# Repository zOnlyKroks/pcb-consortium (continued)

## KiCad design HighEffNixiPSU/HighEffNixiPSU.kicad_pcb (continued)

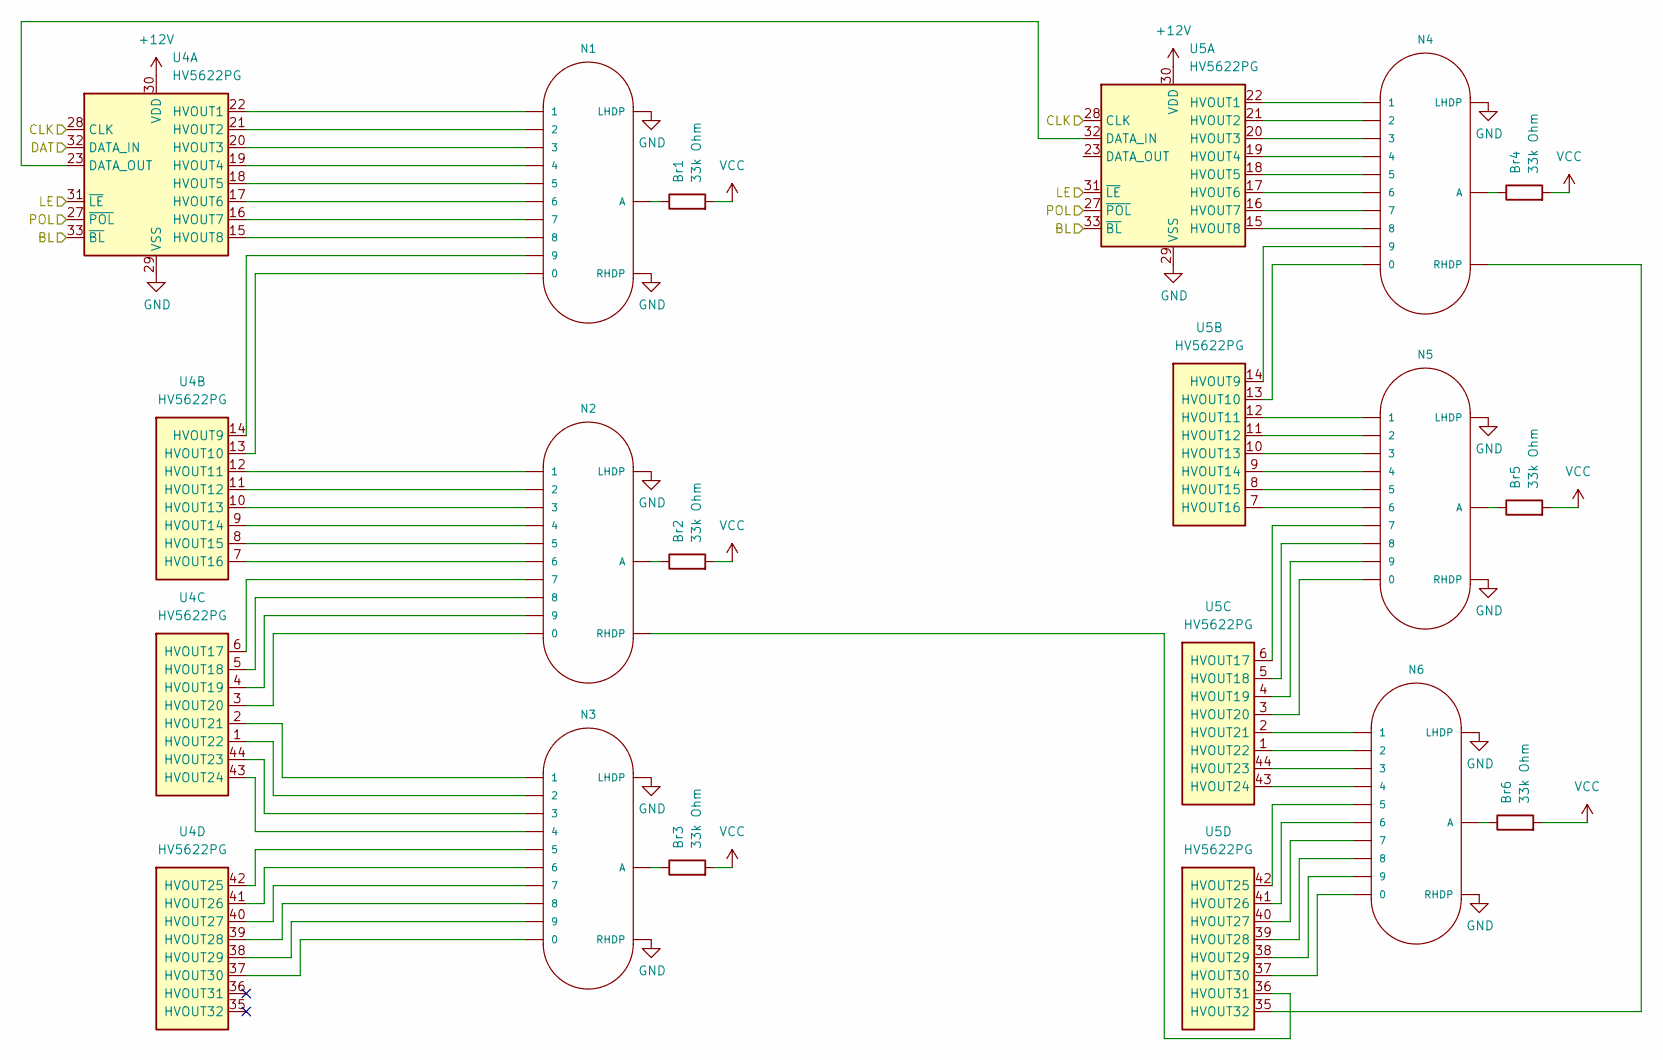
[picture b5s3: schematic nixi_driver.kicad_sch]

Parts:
Br1, Br2, Br3, Br4, Br5, Br6: 33k Ohm; R_1210_3225Metric; LCSC Part # C2775731
N1, N2, N3, N4, N5, N6: IN-16; nixies-us-IN-16
U4, U5: HV5622PG; PQFP-44_10x10mm_P0.8mm; LCSC Part # C220637

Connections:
+12V: U4.30 (VDD), U5.30 (VDD); also elsewhere on the board
/mcu/BL: U4.33 (~BL), U5.33 (~BL); also elsewhere on the board
/mcu/CLK: U4.28 (CLK), U5.28 (CLK); also elsewhere on the board
/mcu/DAT: U4.32 (DATA_IN); also elsewhere on the board
/mcu/LE: U4.31 (~LE), U5.31 (~LE); also elsewhere on the board
/mcu/POL: U4.27 (~POL), U5.27 (~POL); also elsewhere on the board
GND: N1.LHDP, N1.RHDP, N2.LHDP, N3.LHDP, N3.RHDP, N4.LHDP, N5.LHDP, N5.RHDP, N6.LHDP, N6.RHDP, U4.29 (VSS), U5.29 (VSS); also elsewhere on the board
unnamed: Br1.1, N1.A
unnamed: Br2.1, N2.A
unnamed: Br3.1, N3.A
unnamed: Br4.1, N4.A
unnamed: Br5.1, N5.A
unnamed: Br6.1, N6.A
unnamed: U4.23 (DATA_OUT), U5.32 (DATA_IN)
unnamed: N1.1, U4.22 (HVOUT1)
unnamed: N1.2, U4.21 (HVOUT2)
unnamed: N1.3, U4.20 (HVOUT3)
unnamed: N1.4, U4.19 (HVOUT4)
unnamed: N1.5, U4.18 (HVOUT5)
unnamed: N1.6, U4.17 (HVOUT6)
unnamed: N1.7, U4.16 (HVOUT7)
unnamed: N1.8, U4.15 (HVOUT8)
unnamed: N1.9, U4.14 (HVOUT9)
unnamed: N1.0, U4.13 (HVOUT10)
unnamed: N2.1, U4.12 (HVOUT11)
unnamed: N2.2, U4.11 (HVOUT12)
unnamed: N2.3, U4.10 (HVOUT13)
unnamed: N2.4, U4.9 (HVOUT14)
unnamed: N2.5, U4.8 (HVOUT15)
unnamed: N2.6, U4.7 (HVOUT16)
unnamed: N2.7, U4.6 (HVOUT17)
unnamed: N2.8, U4.5 (HVOUT18)
unnamed: N2.9, U4.4 (HVOUT19)
unnamed: N2.0, U4.3 (HVOUT20)
unnamed: N3.1, U4.2 (HVOUT21)
unnamed: N3.2, U4.1 (HVOUT22)
unnamed: N3.3, U4.44 (HVOUT23)
unnamed: N3.4, U4.43 (HVOUT24)
unnamed: N3.5, U4.42 (HVOUT25)
unnamed: N3.6, U4.41 (HVOUT26)
unnamed: N3.7, U4.40 (HVOUT27)
unnamed: N3.8, U4.39 (HVOUT28)
unnamed: N3.9, U4.38 (HVOUT29)
unnamed: N3.0, U4.37 (HVOUT30)
unnamed: N4.1, U5.22 (HVOUT1)
unnamed: N4.2, U5.21 (HVOUT2)
unnamed: N4.3, U5.20 (HVOUT3)
unnamed: N4.4, U5.19 (HVOUT4)
unnamed: N4.5, U5.18 (HVOUT5)
unnamed: N4.6, U5.17 (HVOUT6)
unnamed: N4.7, U5.16 (HVOUT7)
unnamed: N4.8, U5.15 (HVOUT8)
unnamed: N4.9, U5.14 (HVOUT9)
unnamed: N4.0, U5.13 (HVOUT10)
unnamed: N5.1, U5.12 (HVOUT11)
unnamed: N5.2, U5.11 (HVOUT12)
unnamed: N5.3, U5.10 (HVOUT13)
unnamed: N5.4, U5.9 (HVOUT14)
unnamed: N5.5, U5.8 (HVOUT15)
unnamed: N5.6, U5.7 (HVOUT16)
unnamed: N5.7, U5.6 (HVOUT17)
unnamed: N5.8, U5.5 (HVOUT18)
unnamed: N5.9, U5.4 (HVOUT19)
unnamed: N5.0, U5.3 (HVOUT20)
unnamed: N6.1, U5.2 (HVOUT21)
unnamed: N6.2, U5.1 (HVOUT22)
unnamed: N6.3, U5.44 (HVOUT23)
unnamed: N6.4, U5.43 (HVOUT24)
unnamed: N6.5, U5.42 (HVOUT25)
unnamed: N6.6, U5.41 (HVOUT26)
unnamed: N6.7, U5.40 (HVOUT27)
unnamed: N6.8, U5.39 (HVOUT28)
unnamed: N6.9, U5.38 (HVOUT29)
unnamed: N6.0, U5.37 (HVOUT30)
unnamed: N2.RHDP, U5.36 (HVOUT31)
unnamed: N4.RHDP, U5.35 (HVOUT32)
VCC: Br1.2, Br2.2, Br3.2, Br4.2, Br5.2, Br6.2; also elsewhere on the board

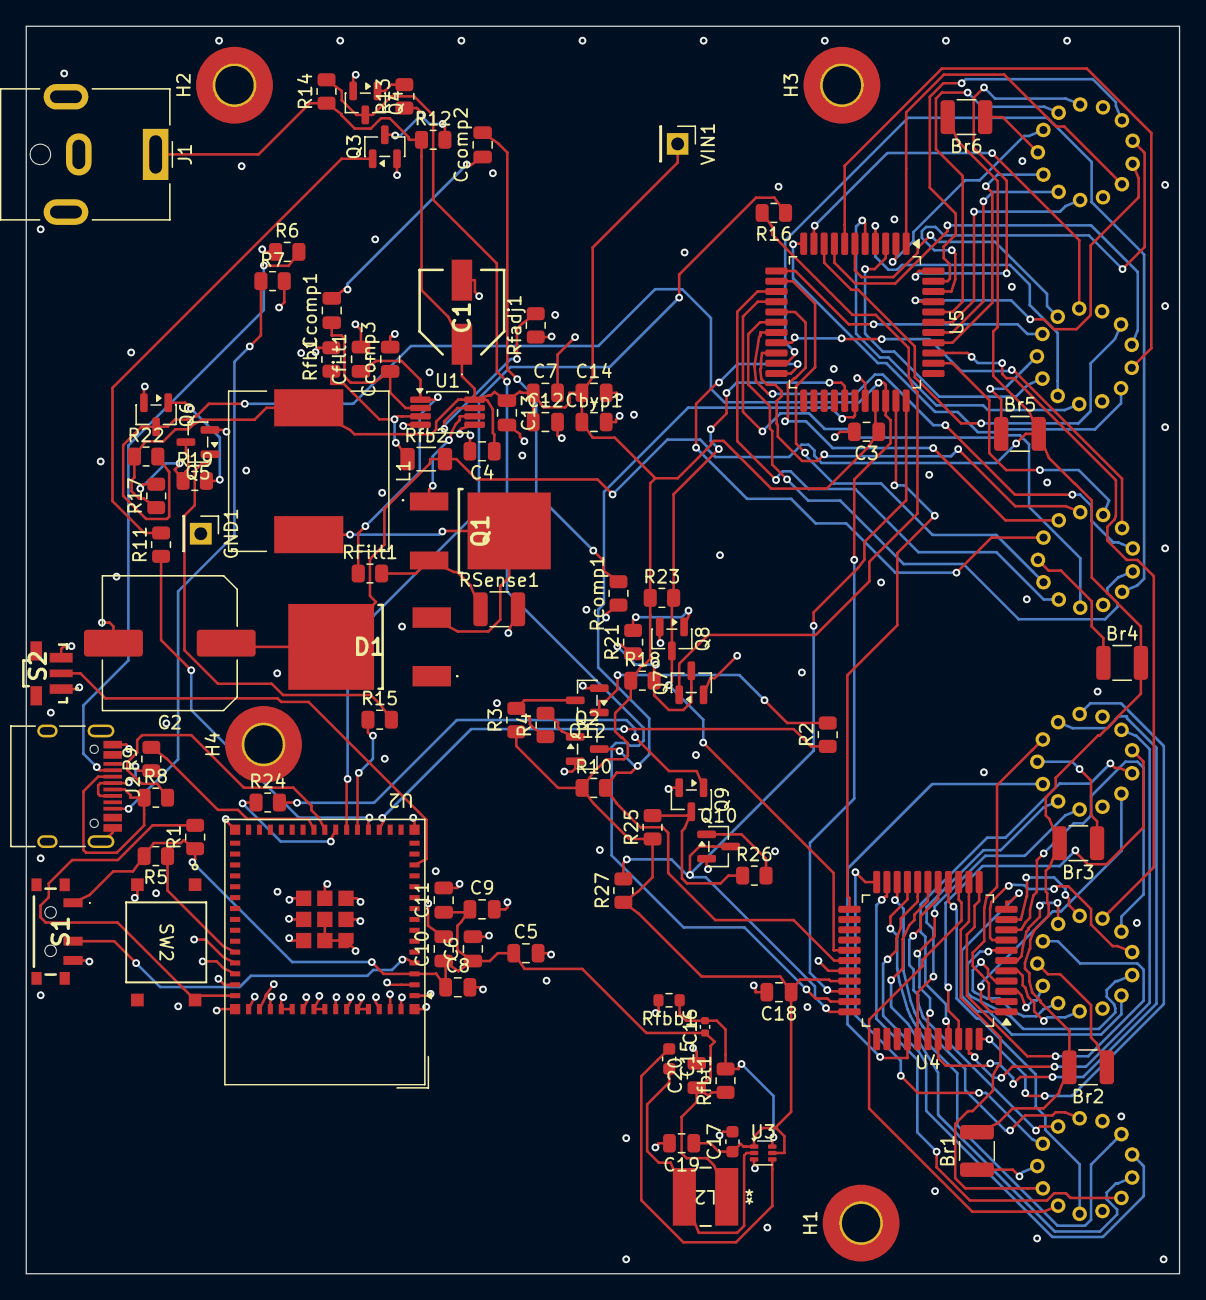
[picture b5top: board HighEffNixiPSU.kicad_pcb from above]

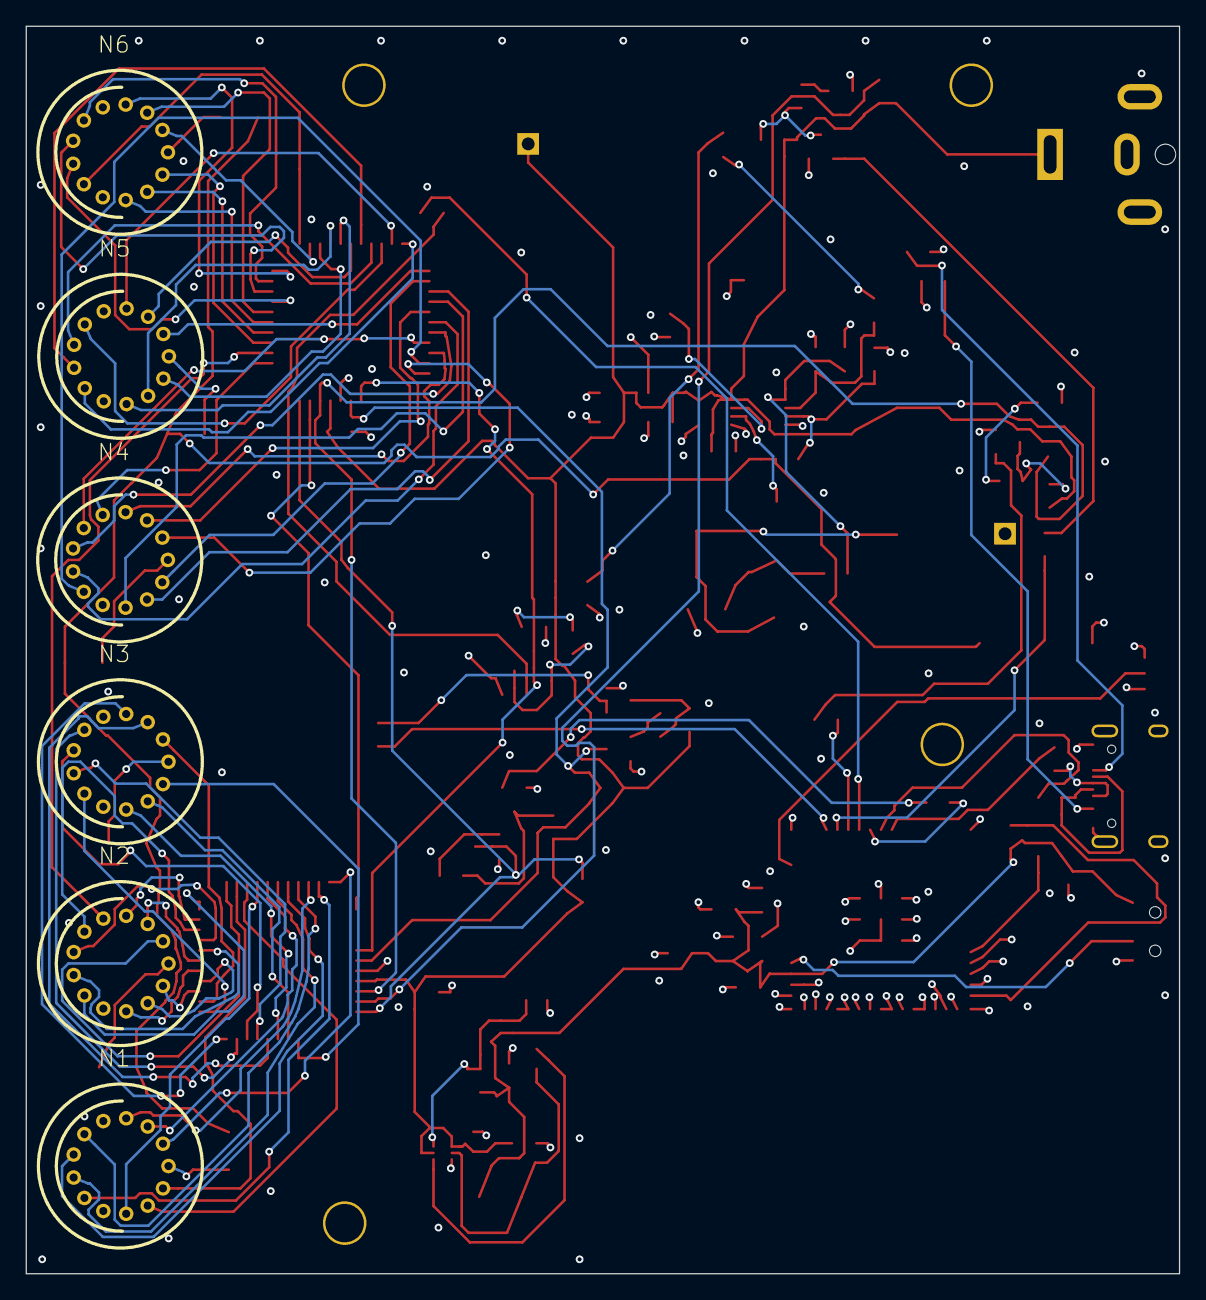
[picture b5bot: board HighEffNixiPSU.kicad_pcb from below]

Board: 4 copper layers, 90.0 x 97.4 mm, 101 parts (6 on the bottom side), 120 nets.

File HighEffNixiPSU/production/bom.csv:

Designator,Footprint,Quantity,Value,LCSC Part #
"BR1, BR2, BR3, BR4, BR5, BR6",1210,6,33k Ohm,C2775731
C1,EEE1AA101SP,1,EEE-FT1V680AP,C413520
"C10, C11, C6, C8, C9",0805,5,100nF,C28233
C5,0805,1,10uF,C15850
CBYP1,0805,1,100nF,C784084
"CCOMP1, CCOMP2",0805,2,1.5nF,C1717
CCOMP3,0805,1,150pF,C2168780
CFILT1,0805,1,10 pF,C107107
D1,STTH506BTR,1,STTH506B,C283501
"GND1, VIN1",PinHeader_1x01_P2.54mm_Vertical,2,Conn_01x01,C492400
IC1,SOT230P700X180-4N,1,AZ1117CH-3.3TRG1,C92102
J1,BarrelJack_CUI_PJ-063AH_Horizontal,1,Jack-DC,C22434582
J2,USB_C_Receptacle_HRO_TYPE-C-31-M-12,1,USB_C_Receptacle_USB2.0,C165948
L1,CYH127-330UH,1,CYH127-330UH,C2929508
"N1, N2, N3, N4, N5, N6",nixies-us-IN-16,6,IN-16,
Q1,FQD16N25CTM,1,FQD16N25CTM,C415866
"Q10, Q12, Q2, Q3, Q4, Q5, Q6, Q7, Q8, Q9",SOT-23,10,MMBTA06,C20069139
"R1, R11, R12, R13, R15, R16, R17, R18, R19, R2, R21, R24, R25, R26, R3, R4, R5",0805,17,10k,C17414
"R10, R14, R22, R23, R27",0805,5,4.7k,C17673
"R6, R7",0805,2,5.1k,C27834
"R8, R9",0805,2,22,C17561
RCOMP1,0805,1,162 kOhm,C47115899
RFADJ1,0805,1,147 kOhm,C47115874
RFB1,0805,1,8.06 kOhm,C857074
RFB2,1206,1,1.2MOhm,C36337
RFILT1,0805,1,100 Ohm,C17408
RSENSE1,1210,1,33 mOhm,C723419
S1,SSSS811101,1,SSSS811101,C109335
S2,TL3340,1,TL3340AF160QG,C2886925
SW2,KH-6X6X5H-STM_SKE,1,EN,C2837531 
U1,VSSOP-8_3x3mm_P0.65mm,1,LM3478MM,C9404
U2,ESP32-S2-MINI-1,1,ESP32-S3-MINI-1,C2913206 
"U4, U5",PQFP-44_10x10mm_P0.8mm,2,HV5622PG,C220637

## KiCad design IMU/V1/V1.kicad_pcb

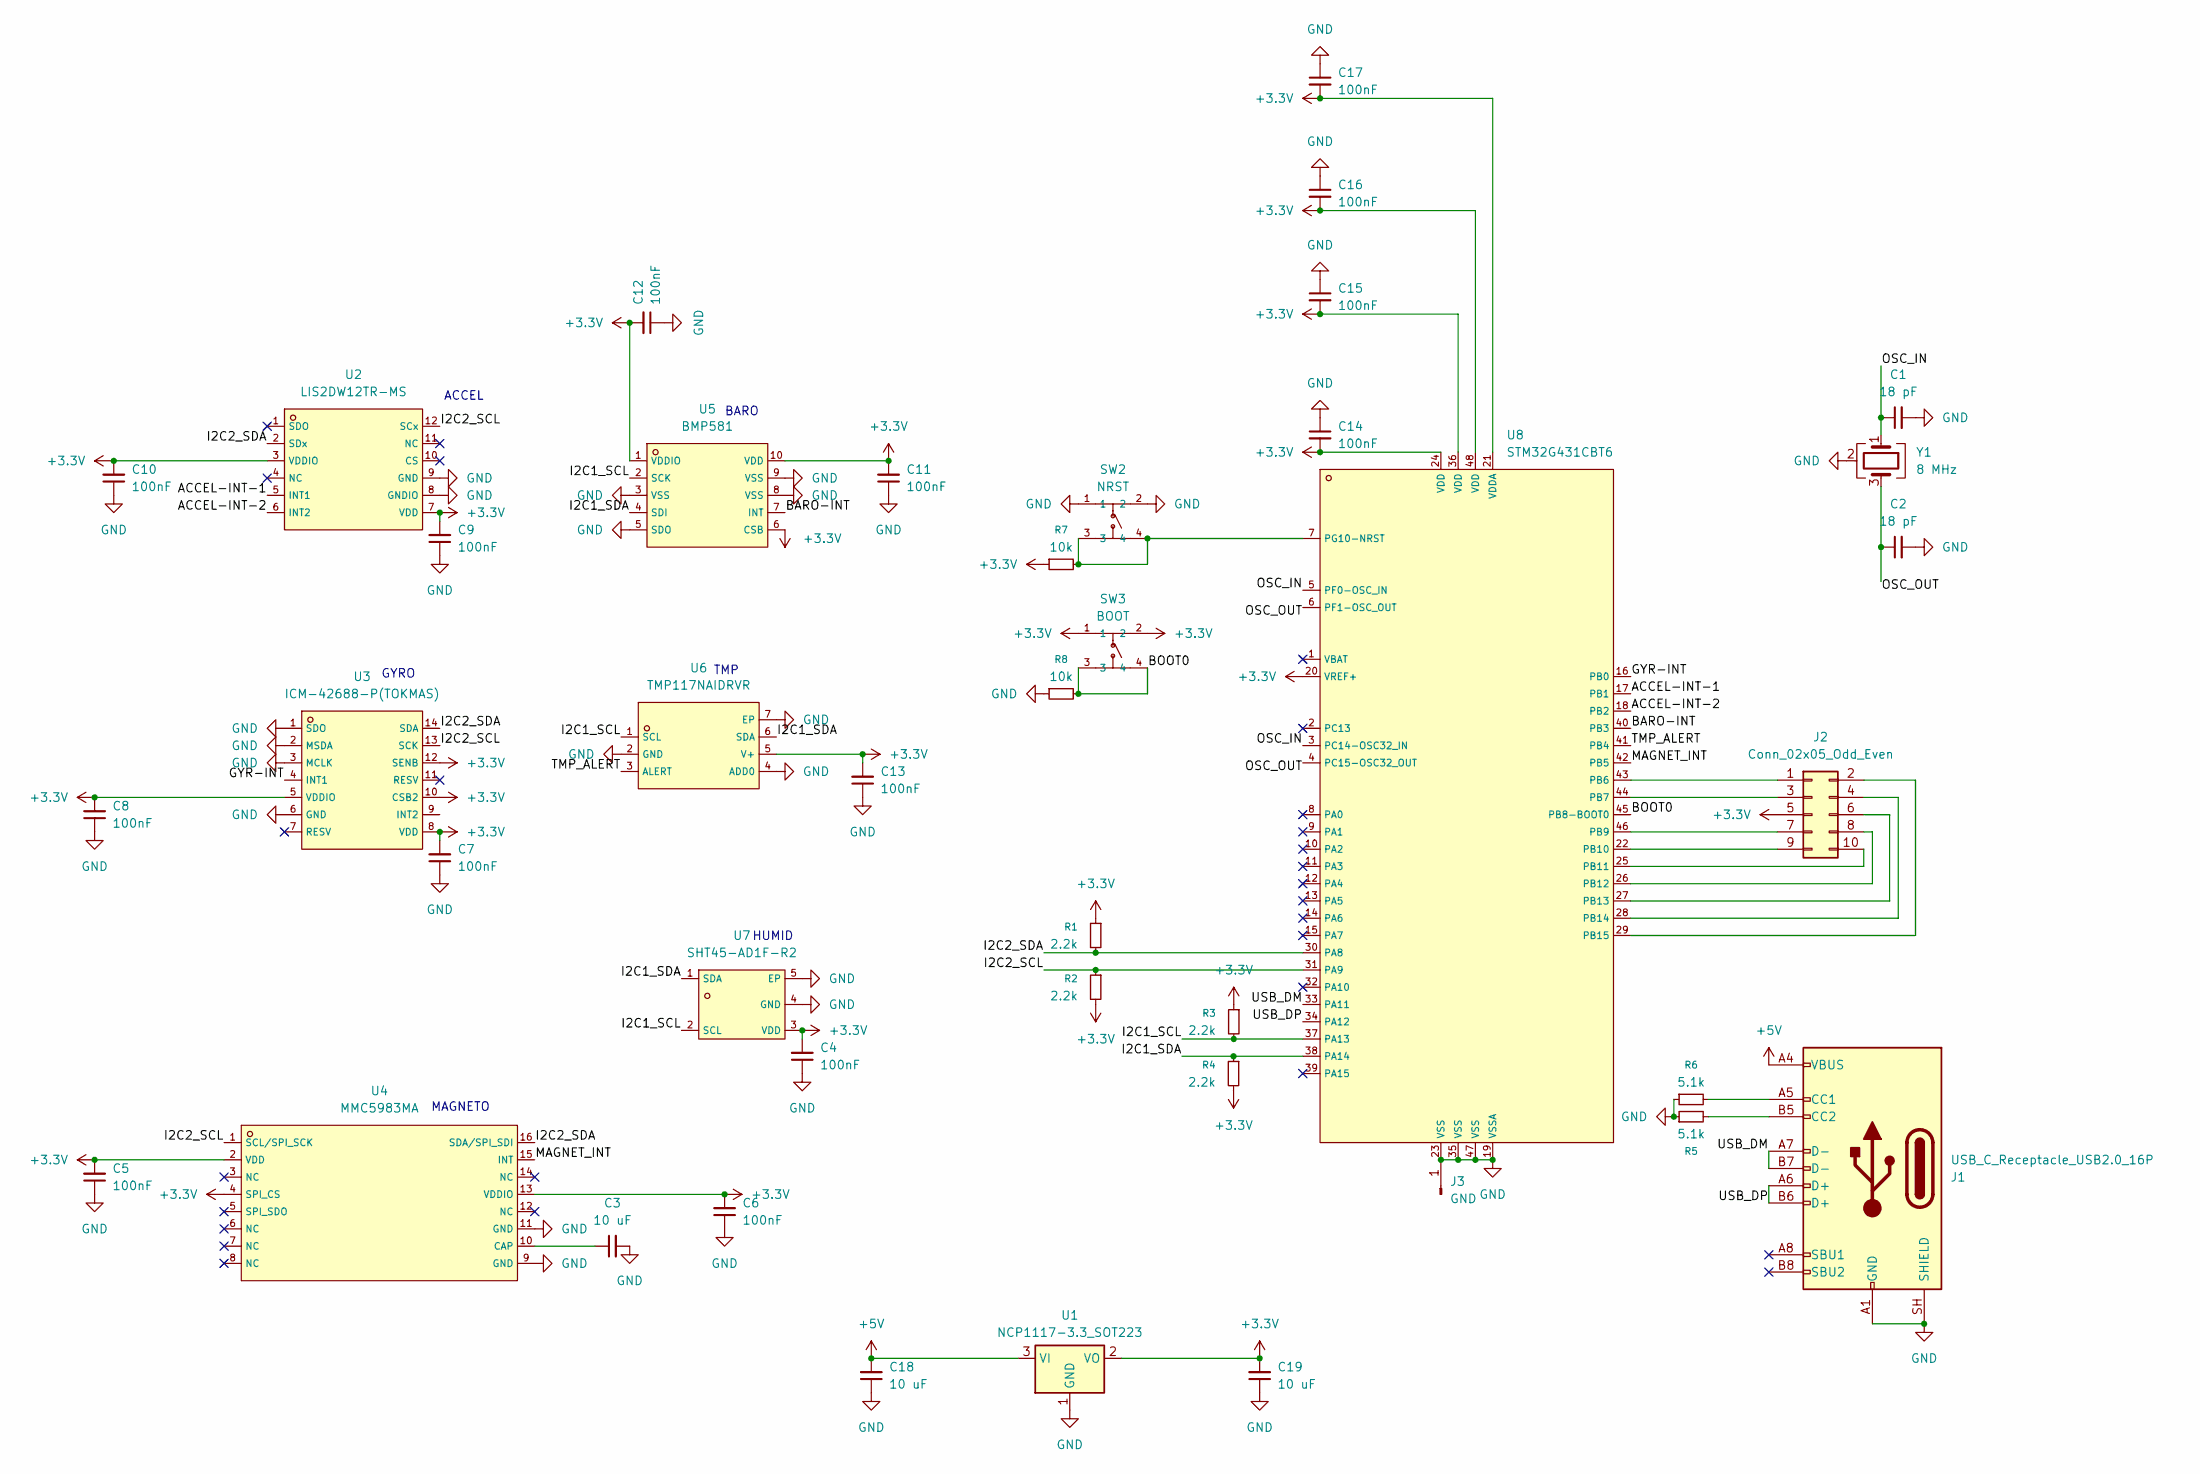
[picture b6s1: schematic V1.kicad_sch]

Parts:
C1, C2: 18 pF; C_0603_1608Metric
C3, C18, C19: 10 uF; C_0805_2012Metric
C4, C5, C6, C7, C8, C9, C10, C11, C12, C13, C14, C15, C16, C17: 100nF; C_0603_1608Metric
J1: USB_C_Receptacle_USB2.0_16P; USB_C_Receptacle_HRO_TYPE-C-31-M-12
J2: Conn_02x05_Odd_Even; PinHeader_2x05_P2.54mm_Vertical
J3: GND; PinHeader_1x01_P2.54mm_Vertical
R1, R2, R3, R4: 2.2k; R_0603_1608Metric
R5, R6: 5.1k; R_0603_1608Metric
R7, R8: 10k; R_0603_1608Metric
SW2: NRST; C2837531_SW-SMD_4P-L6_0-W6_0-P4_50-LS9_0_H5_0; LCSC C2837531
SW3: BOOT; C2837531_SW-SMD_4P-L6_0-W6_0-P4_50-LS9_0_H5_0; LCSC C2837531
U1: NCP1117-3.3_SOT223; SOT-223-3_TabPin2
U2: LIS2DW12TR-MS; C50385411_LGA-12_L2_0-W2_0_BMA250; LCSC C50385411
U3: ICM-42688-P(TOKMAS); C54308212_LGA-14_L3_0-W2_5-P0_50-BL; LCSC C54308212
U4: MMC5983MA; C404329_LGA-16_L3_0-W3_0-P0_50-BL_SQ; LCSC C404329
U5: BMP581; C5362283_LGA-10_L2_0-W2_0-P0_50-TL_BMP581; LCSC C5362283
U6: TMP117NAIDRVR; C2876169_WSON-6_L2_0-W2_0-P0_65-TL-EP; LCSC C2876169
U7: SHT45-AD1F-R2; C5360602_DFN-4_L1_5-W1_5-P0_8-TL-EP; LCSC C5360602
U8: STM32G431CBT6; C529355_LQFP-48_L7_0-W7_0-P0_50-LS9_0-BL; LCSC C529355
Y1: 8 MHz; Crystal_SMD_3225-4Pin_3.2x2.5mm

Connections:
+3.3V: C4.2, C5.2, C6.2, C7.2, C8.2, C9.2, C10.2, C11.2, C12.2, C13.2, C14.2, C15.2, C16.2, C17.2, C19.2, J2.5, R1.1, R2.2, R3.1, R4.2, R7.1, SW3.1, SW3.2, U1.2 (VO), U2.3 (VDDIO), U2.7 (VDD), U3.5 (VDDIO), U3.8 (VDD), U3.10 (CSB2), U3.12 (SENB), U4.2 (VDD), U4.4 (SPI_CS), U4.13 (VDDIO), U5.1 (VDDIO), U5.6 (CSB), U5.10 (VDD), U6.5 (V+), U7.3 (VDD), U8.20 (VREF+), U8.21 (VDDA), U8.24 (VDD), U8.36 (VDD), U8.48 (VDD)
+5V: C18.2, J1.A4 (VBUS), J1.A9 (VBUS), J1.B4 (VBUS), J1.B9 (VBUS), U1.3 (VI)
/ACCEL-INT-1: U2.5 (INT1), U8.17 (PB1)
/ACCEL-INT-2: U2.6 (INT2), U8.18 (PB2)
/BARO-INT: U5.7 (INT), U8.40 (PB3)
/BOOT0: R8.2, SW3.3, SW3.4, U8.45 (PB8-BOOT0)
/GYR-INT: U3.4 (INT1), U8.16 (PB0)
/I2C1_SCL: R3.2, U5.2 (SCK), U6.1 (SCL), U7.2 (SCL), U8.37 (PA13)
/I2C1_SDA: R4.1, U5.4 (SDI), U6.6 (SDA), U7.1 (SDA), U8.38 (PA14)
/I2C2_SCL: R2.1, U2.12 (SCx), U3.13 (SCK), U4.1 (SCL/SPI_SCK), U8.31 (PA9)
/I2C2_SDA: R1.2, U2.2 (SDx), U3.14 (SDA), U4.16 (SDA/SPI_SDI), U8.30 (PA8)
/MAGNET_INT: U4.15 (INT), U8.42 (PB5)
/OSC_IN: C1.1, U8.3 (PC14-OSC32_IN), U8.5 (PF0-OSC_IN), Y1.1
/OSC_OUT: C2.1, U8.4 (PC15-OSC32_OUT), U8.6 (PF1-OSC_OUT), Y1.3
/TMP_ALERT: U6.3 (ALERT), U8.41 (PB4)
/USB_DM: J1.A7 (D-), J1.B7 (D-), U8.33 (PA11)
/USB_DP: J1.A6 (D+), J1.B6 (D+), U8.34 (PA12)
GND: C1.2, C2.2, C3.2, C4.1, C5.1, C6.1, C7.1, C8.1, C9.1, C10.1, C11.1, C12.1, C13.1, C14.1, C15.1, C16.1, C17.1, C18.1, C19.1, J1.A1 (GND), J1.A12 (GND), J1.B1 (GND), J1.B12 (GND), J1.SH (SHIELD), J3.1 (Pin_1_1), R5.1, R6.1, R8.1, SW2.1, SW2.2, U1.1 (GND), U2.8 (GNDIO), U2.9 (GND), U3.1 (SDO), U3.2 (MSDA), U3.3 (MCLK), U3.6 (GND), U4.9 (GND), U4.11 (GND), U5.3 (VSS), U5.5 (SDO), U5.8 (VSS), U5.9 (VSS), U6.2 (GND), U6.4 (ADD0), U6.7 (EP), U7.4 (GND), U7.5 (EP), U8.19 (VSSA), U8.23 (VSS), U8.35 (VSS), U8.47 (VSS), Y1.2 (G), Y1.4 (G)
unnamed: J1.A5 (CC1), R6.2
unnamed: J1.B5 (CC2), R5.2
unnamed: J2.1, U8.43 (PB6)
unnamed: J2.2, U8.29 (PB15)
unnamed: J2.3, U8.44 (PB7)
unnamed: J2.4, U8.28 (PB14)
unnamed: J2.6, U8.27 (PB13)
unnamed: J2.7, U8.46 (PB9)
unnamed: J2.8, U8.26 (PB12)
unnamed: J2.9, U8.22 (PB10)
unnamed: J2.10, U8.25 (PB11)
unnamed: C3.1, U4.10 (CAP)
unnamed: R7.2, SW2.3, SW2.4, U8.7 (PG10-NRST)

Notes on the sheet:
HUMID
TMP
GYRO
MAGNETO
BARO
ACCEL

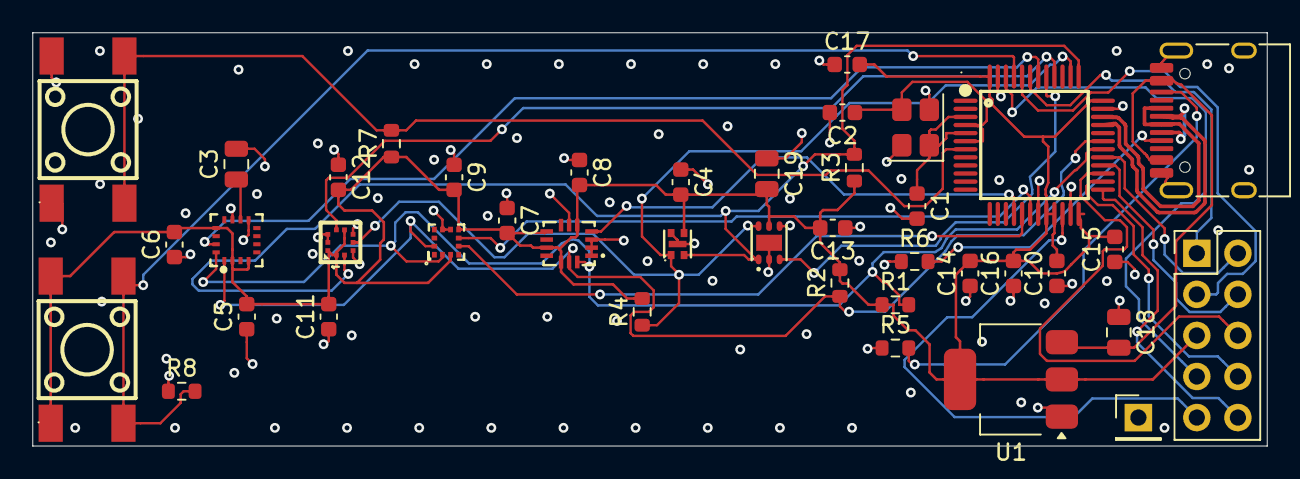
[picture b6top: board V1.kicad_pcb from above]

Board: 4 copper layers, 76.3 x 25.6 mm, 41 parts (0 on the bottom side), 31 nets.
